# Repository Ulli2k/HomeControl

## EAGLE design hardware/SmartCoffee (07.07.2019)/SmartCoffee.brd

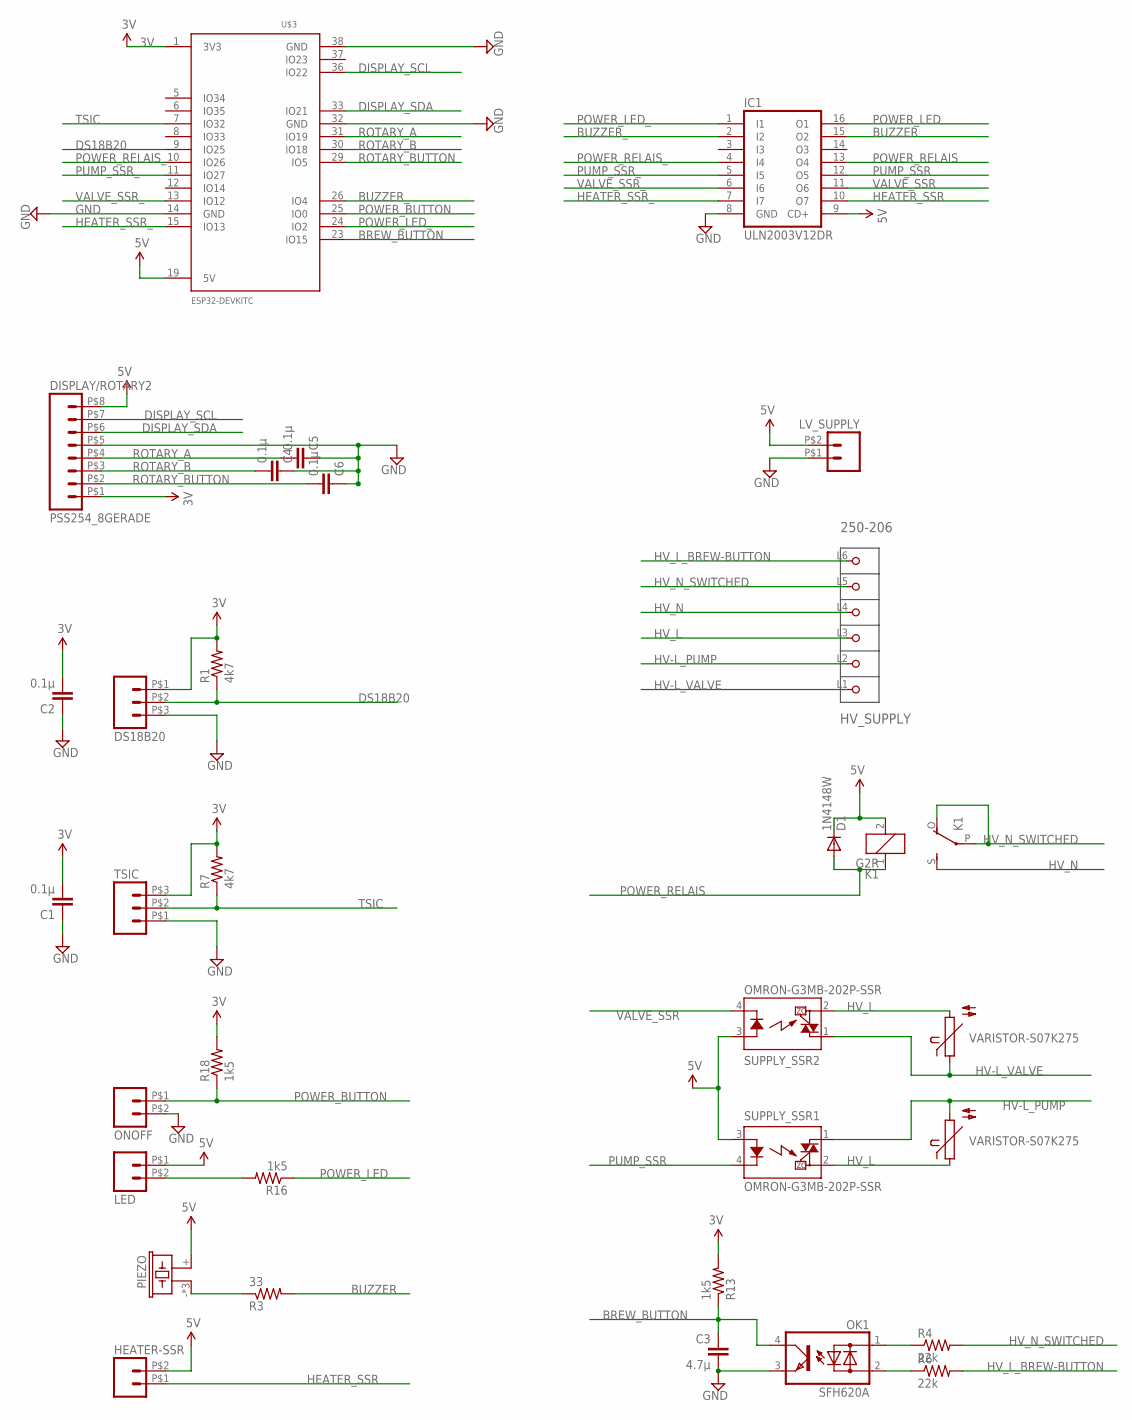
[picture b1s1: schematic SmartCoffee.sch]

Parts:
C1, C2, C4, C5, C6: 0.1µ; 0603-CAP
C3: 4.7µ; 0805-CAP
D1: 1N4148W; SOD123
DISPLAY/ROTARY2: PSS254_8GERADE; 08G
DS18B20: PSS254_3GERADE; 03G
HEATER-SSR: PSS254_2GERADE; 02G
HV_SUPPLY: 250-206; P-250-206
IC1: ULN2003V12DR; SO16
K1: G2R
LED: PSS254_2GERADE; 02G
LV_SUPPLY: PSS254_2GERADE; 02G
OK1: SFH620A; DIL04
ONOFF: PSS254_2GERADE; 02G
PIEZO: BUZZER-PIEZO_SMD
R1, R7: 4k7; 0603-RES
R3: 33; 0603-RES
R4, R6: 22k; RES_UPRIGHT
R5, R8: VARISTOR-S07K275; S07K275
R13, R16, R18: 1k5; 0603-RES
SUPPLY_SSR1, SUPPLY_SSR2: OMRON-G3MB-202P-SSR
TSIC: PSS254_3GERADE; 03G
U$3: ESP32DEVKITC; ESP32-DEVKITC

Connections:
3V: C1.2, C2.2, DISPLAY/ROTARY2.P$1 (1), DS18B20.P$1 (1), R1.2, R7.2, R13.2, R18.2, TSIC.P$3 (3), U$3.1 (3V3)
BREW_BUTTON: C3.1, OK1.4 (C), R13.1, U$3.23 (IO15)
BUZZER: IC1.15 (O2), R3.2
BUZZER_: IC1.2 (I2), U$3.26 (IO4)
DISPLAY_SCL: DISPLAY/ROTARY2.P$7 (7), U$3.36 (IO22)
DISPLAY_SDA: DISPLAY/ROTARY2.P$6 (6), U$3.33 (IO21)
DS18B20: DS18B20.P$2 (2), R1.1, U$3.9 (IO25)
GND: C1.1, C2.1, C3.2, C4.1, C5.1, C6.1, DISPLAY/ROTARY2.P$5 (5), DS18B20.P$3 (3), IC1.8 (GND), LV_SUPPLY.P$1 (1), OK1.3 (E), ONOFF.P$2 (2), TSIC.P$1 (1), U$3.14 (GND), U$3.32 (GND), U$3.38 (GND)
HEATER_SSR: HEATER-SSR.P$1 (1), IC1.10 (O7)
HEATER_SSR_: IC1.7 (I7), U$3.15 (IO13)
HV-L_PUMP: HV_SUPPLY.L2 (P2), R8.2, SUPPLY_SSR1.1 (DS1)
HV-L_VALVE: HV_SUPPLY.L1 (P1), R5.1, SUPPLY_SSR2.1 (DS1)
HV_L: HV_SUPPLY.L3 (P3), R5.2, R8.1, SUPPLY_SSR1.2 (DS2), SUPPLY_SSR2.2 (DS2)
HV_L_BREW-BUTTON: HV_SUPPLY.L6 (P6), R6.2
HV_N: HV_SUPPLY.L4 (P4), K1.S
HV_N_SWITCHED: HV_SUPPLY.L5 (P5), K1.O, K1.P, R4.2
unnamed: LED.P$2 (2), R16.2
unnamed: OK1.1 (AC1), R4.1
unnamed: PIEZO.- (2), PIEZO.DUMMY (2), PIEZO.DUMMY1 (2), R3.1
unnamed: OK1.2 (AC2), R6.1
POWER_BUTTON: ONOFF.P$1 (1), R18.1, U$3.25 (IO0)
POWER_LED: IC1.16 (O1), R16.1
POWER_LED_: IC1.1 (I1), U$3.24 (IO2)
POWER_RELAIS: D1.A, IC1.13 (O4), K1.1
POWER_RELAIS_: IC1.4 (I4), U$3.10 (IO26)
PUMP_SSR: IC1.12 (O5), SUPPLY_SSR1.4 (K)
PUMP_SSR_: IC1.5 (I5), U$3.11 (IO27)
ROTARY_A: C5.2, DISPLAY/ROTARY2.P$4 (4), U$3.31 (IO19)
ROTARY_B: C4.2, DISPLAY/ROTARY2.P$3 (3), U$3.30 (IO18)
ROTARY_BUTTON: C6.2, DISPLAY/ROTARY2.P$2 (2), U$3.29 (IO5)
TSIC: R7.1, TSIC.P$2 (2), U$3.7 (IO32)
VALVE_SSR: IC1.11 (O6), SUPPLY_SSR2.4 (K)
VALVE_SSR_: IC1.6 (I6), U$3.13 (IO12)
VCC: D1.C, DISPLAY/ROTARY2.P$8 (8), HEATER-SSR.P$2 (2), IC1.9 (CD+), K1.2, LED.P$1 (1), LV_SUPPLY.P$2 (2), PIEZO.+ (1), SUPPLY_SSR1.3 (A), SUPPLY_SSR2.3 (A), U$3.19 (5V)

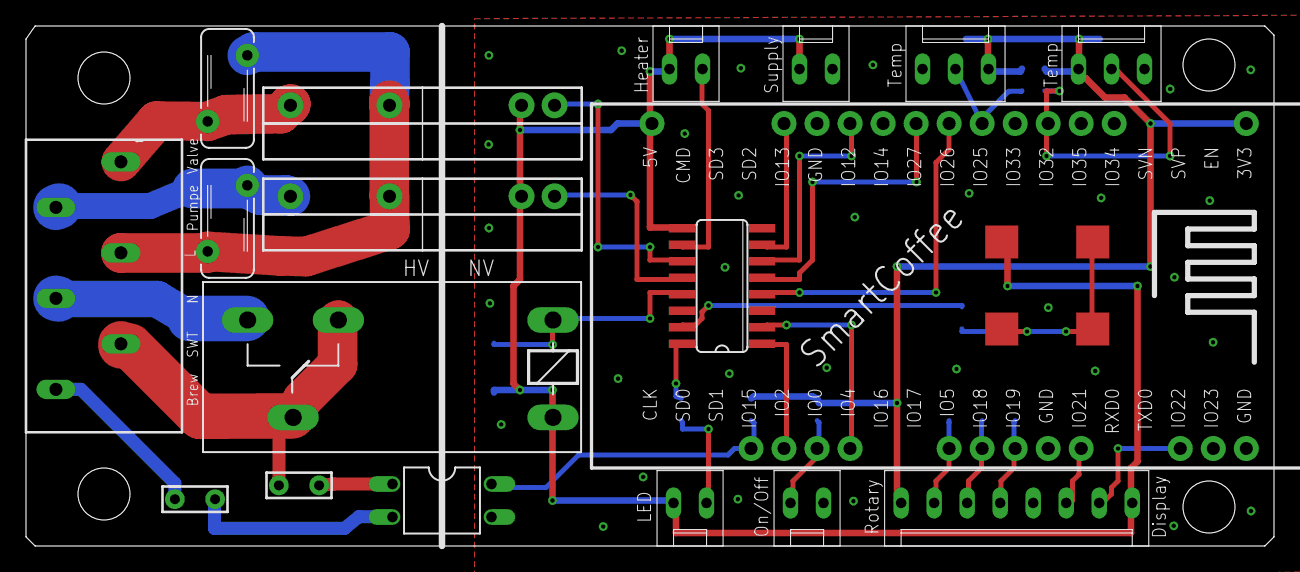
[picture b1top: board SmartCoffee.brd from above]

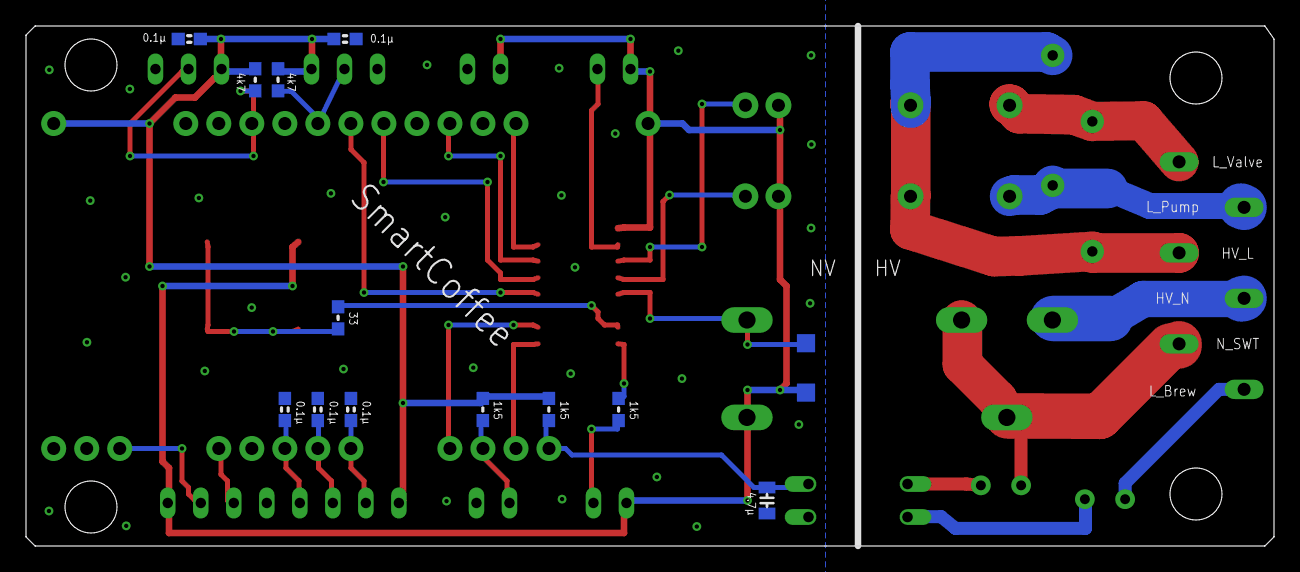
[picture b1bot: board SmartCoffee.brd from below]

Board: 2 copper layers, 96.0 x 40.0 mm, 32 parts (13 on the bottom side), 34 nets.

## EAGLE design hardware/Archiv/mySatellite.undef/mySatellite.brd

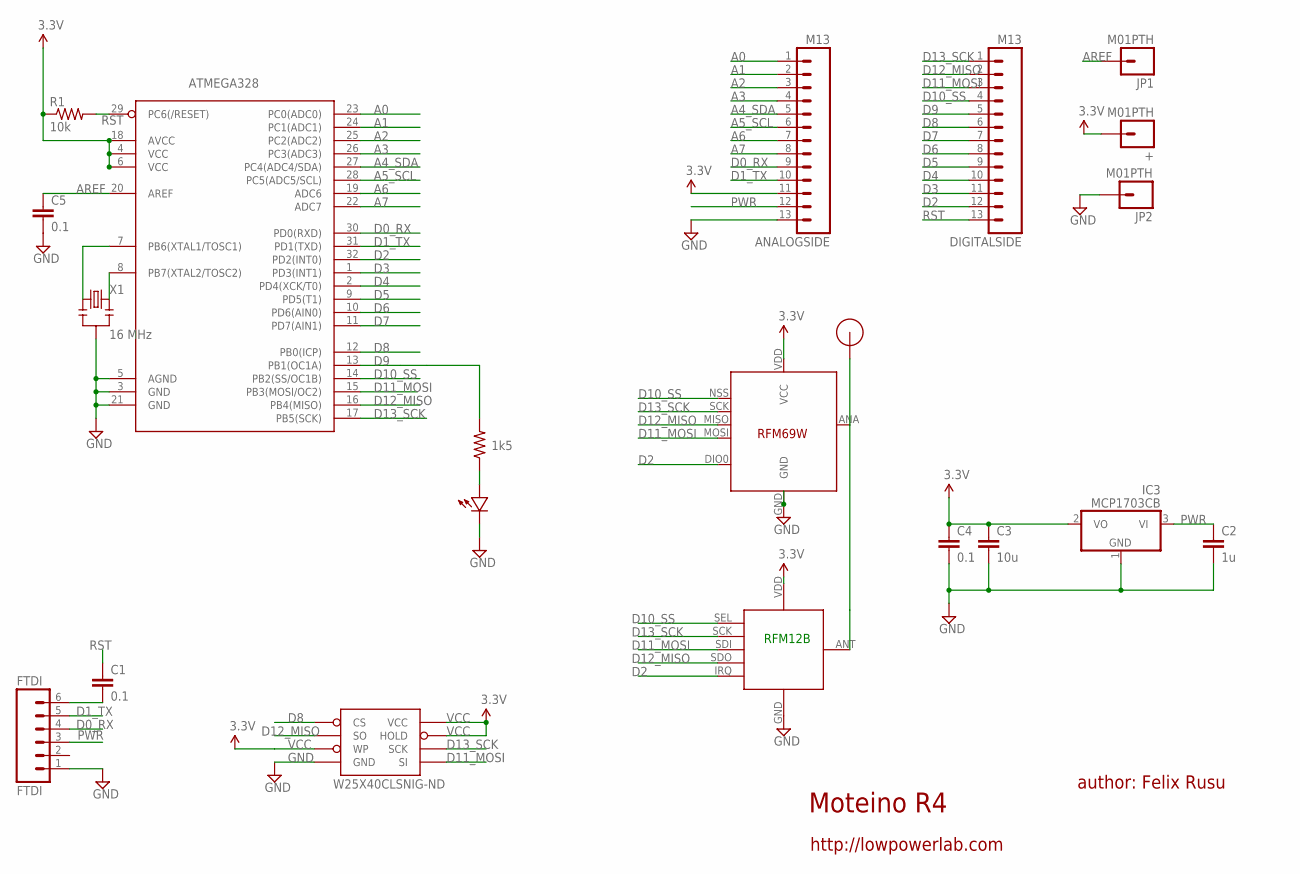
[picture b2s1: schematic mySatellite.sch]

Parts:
+: M01PTH; 1X01
ANALOGSIDE: M13; 1X13
ATMEGA328: ATMega-328; TQFP32-08
C1, C4, C5: 0.1; 0603-CAP
C2: 1u; 0603-CAP
C3: 10u; 0805-CAP
DIGITALSIDE: M13; 1X13
FTDI: FTDI; 1X06
IC3: MCP1703CB; SOT23
JP1, JP2: M01PTH; 1X01
R1: 10k; 0603-RES
R2: 1k5; 0603-RES
RFM12B: RFM12B_MINPADS; RFM12B-MINPADS
U$1: RFM12B_ANTENNA; RFM12B-ANTENNA
U$2: LED0603; 0603-LED
U$5: RFM69; RFM69W-MINPADS
W25X40CLSNIG-ND: AT25F512BWIDE_5.3MM; SO08WIDE
X1: 16 MHz; RESONATOR-SMD

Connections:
A0: ANALOGSIDE.1, ATMEGA328.23 (PC0(ADC0))
A1: ANALOGSIDE.2, ATMEGA328.24 (PC1(ADC1))
A2: ANALOGSIDE.3, ATMEGA328.25 (PC2(ADC2))
A3: ANALOGSIDE.4, ATMEGA328.26 (PC3(ADC3))
A4_SDA: ANALOGSIDE.5, ATMEGA328.27 (PC4(ADC4/SDA))
A5_SCL: ANALOGSIDE.6, ATMEGA328.28 (PC5(ADC5/SCL))
A6: ANALOGSIDE.7, ATMEGA328.19 (ADC6)
A7: ANALOGSIDE.8, ATMEGA328.22 (ADC7)
AREF: ATMEGA328.20 (AREF), C5.1, JP1.1
D0_RX: ANALOGSIDE.9, ATMEGA328.30 (PD0(RXD)), FTDI.4
D1_TX: ANALOGSIDE.10, ATMEGA328.31 (PD1(TXD)), FTDI.5
D2: ATMEGA328.32 (PD2(INT0)), DIGITALSIDE.12, RFM12B.IRQ, U$5.DIO0
D3: ATMEGA328.1 (PD3(INT1)), DIGITALSIDE.11
D4: ATMEGA328.2 (PD4(XCK/T0)), DIGITALSIDE.10
D5: ATMEGA328.9 (PD5(T1)), DIGITALSIDE.9
D6: ATMEGA328.10 (PD6(AIN0)), DIGITALSIDE.8
D7: ATMEGA328.11 (PD7(AIN1)), DIGITALSIDE.7
D8: ATMEGA328.12 (PB0(ICP)), DIGITALSIDE.6, W25X40CLSNIG-ND.1 (CS)
D9: ATMEGA328.13 (PB1(OC1A)), DIGITALSIDE.5, R2.2
D10_SS: ATMEGA328.14 (PB2(SS/OC1B)), DIGITALSIDE.4, RFM12B.SEL, U$5.NSS (SEL)
D11_MOSI: ATMEGA328.15 (PB3(MOSI/OC2)), DIGITALSIDE.3, RFM12B.SDI (SDI/MOSI), U$5.MOSI, W25X40CLSNIG-ND.5 (SI)
D12_MISO: ATMEGA328.16 (PB4(MISO)), DIGITALSIDE.2, RFM12B.SDO (SDO/MISO), U$5.MISO, W25X40CLSNIG-ND.2 (SO)
D13_SCK: ATMEGA328.17 (PB5(SCK)), DIGITALSIDE.1, RFM12B.SCK, U$5.SCK, W25X40CLSNIG-ND.6 (SCK)
GND: ANALOGSIDE.13, ATMEGA328.3 (GND), ATMEGA328.5 (AGND), ATMEGA328.21 (GND), C2.2, C3.2, C4.2, C5.2, FTDI.1, IC3.1 (GND), JP2.1, RFM12B.GND, U$2.MINUS, U$5.GND, W25X40CLSNIG-ND.4 (GND), X1.2
unnamed: ATMEGA328.7 (PB6(XTAL1/TOSC1)), X1.1
unnamed: R2.1, U$2.PLUS
unnamed: RFM12B.ANT, U$1.P$1, U$5.ANA (ANT)
unnamed: C1.2, FTDI.6
unnamed: ATMEGA328.8 (PB7(XTAL2/TOSC2)), X1.3
PWR: ANALOGSIDE.12, C2.1, FTDI.3, IC3.3 (VI)
RST: ATMEGA328.29 (PC6(/RESET)), C1.1, DIGITALSIDE.13, R1.2
VCC: +.1, ANALOGSIDE.11, ATMEGA328.4 (VCC), ATMEGA328.6 (VCC), ATMEGA328.18 (AVCC), C3.1, C4.1, IC3.2 (VO), R1.1, RFM12B.VDD, U$5.VDD (VCC), W25X40CLSNIG-ND.3 (WP), W25X40CLSNIG-ND.7 (HOLD), W25X40CLSNIG-ND.8 (VCC)

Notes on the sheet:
Moteino R4
author: Felix Rusu
http://lowpowerlab.com
RFM12B

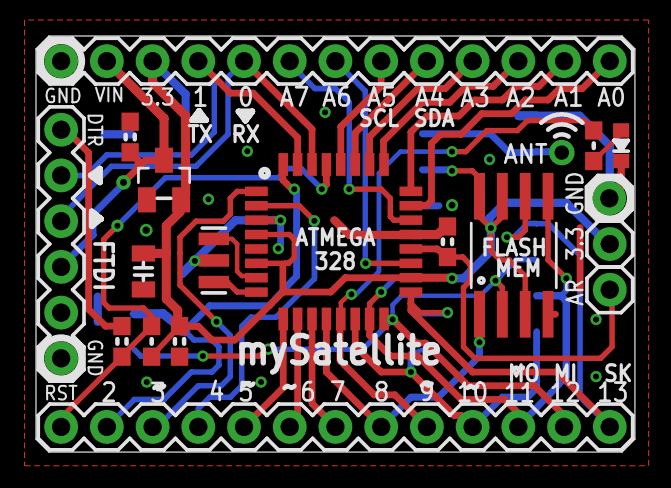
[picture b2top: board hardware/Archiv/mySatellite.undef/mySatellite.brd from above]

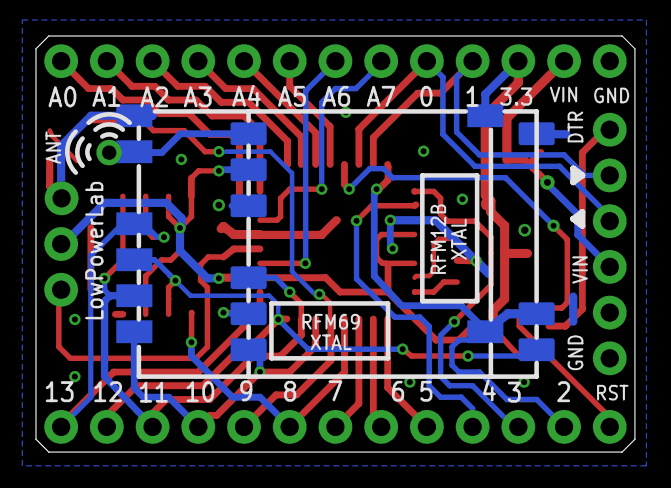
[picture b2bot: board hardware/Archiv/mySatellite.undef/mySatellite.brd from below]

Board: 2 copper layers, 33.3 x 23.1 mm, 21 parts (2 on the bottom side), 32 nets.

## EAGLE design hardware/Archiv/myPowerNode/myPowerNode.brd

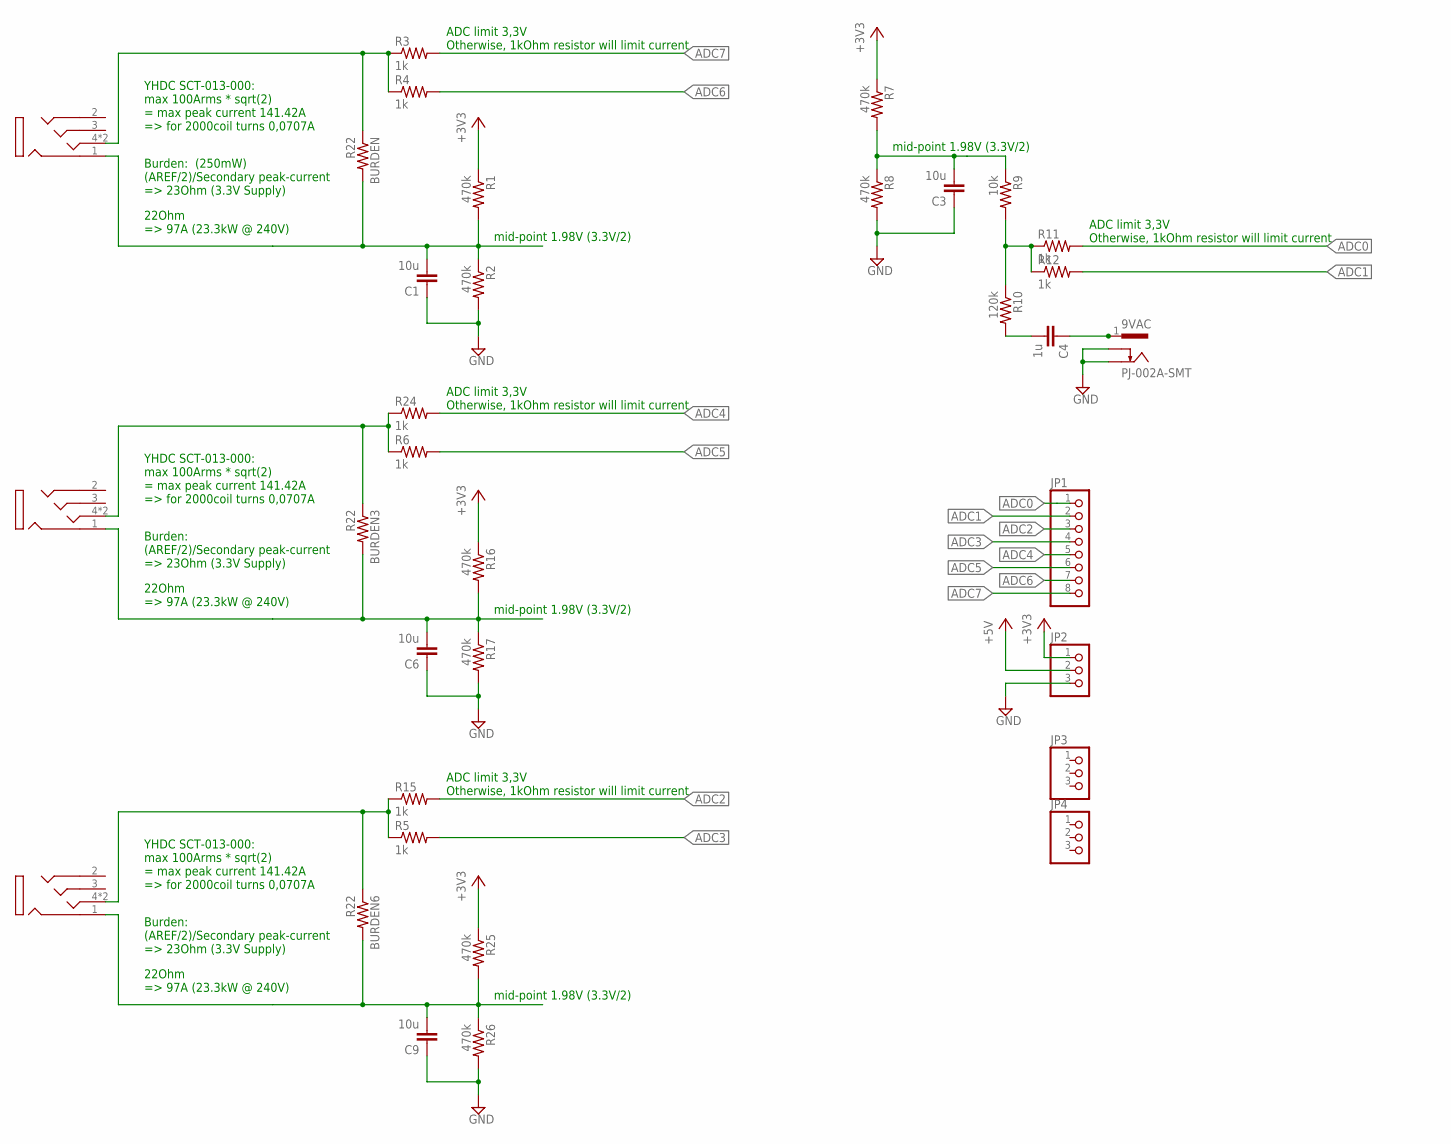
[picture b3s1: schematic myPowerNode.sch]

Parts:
9VAC: PJ-002A-SMT; CUI_PJ-002B-SMT
BURDEN, BURDEN3, BURDEN6: R22; R0805
C1, C3, C6, C9: 10u; 0603-CAP
C4: 1u; 0603-CAP
CT1, CT4, CT7: 1503_13; 1503-03
JP1: PINHD-1X8CLEANBIG; 1X08-CLEANBIG
JP2, JP3, JP4: PINHD-1X3CB; 1X03-CLEANBIG
R1, R2, R7, R8, R16, R17, R25, R26: 470k; 0603-RES
R3, R4, R5, R6, R11, R12, R15, R24: 1k; 0603-RES
R9: 10k; 0603-RES
R10: 120k; 0603-RES

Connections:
+3V3: JP2.1, R1.1, R7.1, R16.1, R25.1
+5V: JP2.2
ADC0: JP1.1, R11.2
ADC1: JP1.2, R12.2
ADC2: JP1.3, R15.2
ADC3: JP1.4, R5.2
ADC4: JP1.5, R24.2
ADC5: JP1.6, R6.2
ADC6: JP1.7, R4.2
ADC7: JP1.8, R3.2
GND: 9VAC.3, 9VAC.4, C1.1, C3.1, C6.1, C9.1, JP2.3, R2.2, R8.2, R17.2, R26.2
unnamed: BURDEN.2, C1.2, CT1.1, R1.2, R2.1
unnamed: BURDEN.1, CT1.4, CT1.4-2 (4), R3.1, R4.1
unnamed: C3.2, R7.2, R8.1, R9.1
unnamed: R9.2, R10.1, R11.1, R12.1
unnamed: C4.2, R10.2
unnamed: 9VAC.1, 9VAC.2, C4.1
unnamed: BURDEN3.2, C6.2, CT4.1, R16.2, R17.1
unnamed: BURDEN3.1, CT4.4, CT4.4-2 (4), R6.1, R24.1
unnamed: BURDEN6.2, C9.2, CT7.1, R25.2, R26.1
unnamed: BURDEN6.1, CT7.4, CT7.4-2 (4), R5.1, R15.1

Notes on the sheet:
mid-point 1.98V (3.3V/2)
ADC limit 3,3V Otherwise, 1kOhm resistor will limit current
YHDC SCT-013-000: max 100Arms * sqrt(2) = max peak current 141.42A => for 2000coil turns 0,0707A
Burden: (250mW) (AREF/2)/Secondary peak-current => 23Ohm (3.3V Supply)
22Ohm => 97A (23.3kW @ 240V)
Burden: (AREF/2)/Secondary peak-current => 23Ohm (3.3V Supply)

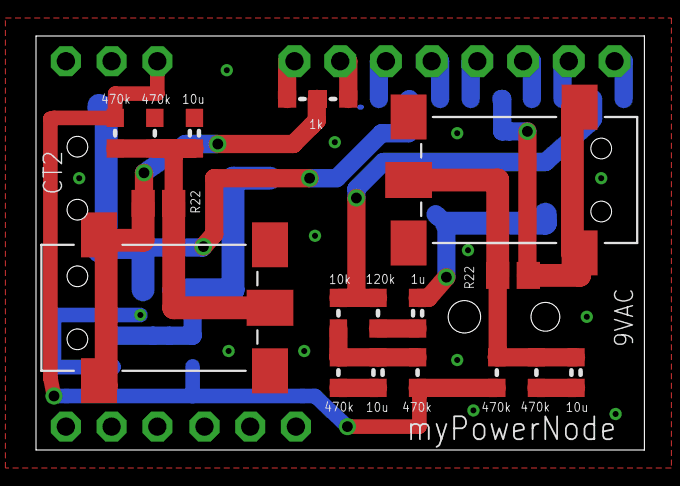
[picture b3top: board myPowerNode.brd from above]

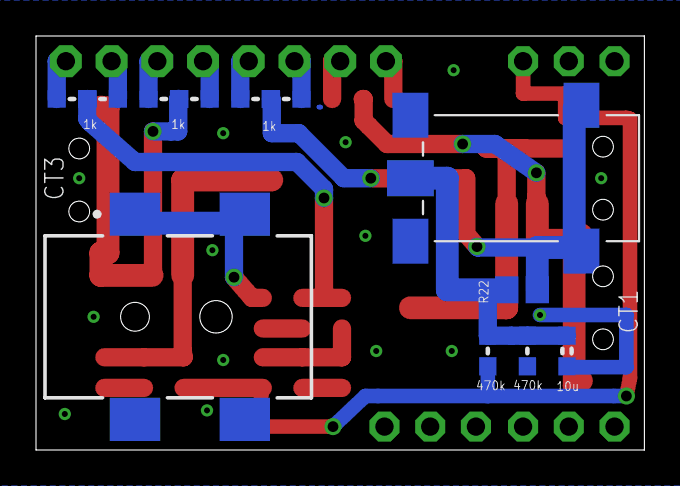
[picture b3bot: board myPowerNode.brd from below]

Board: 2 copper layers, 33.8 x 23.0 mm, 34 parts (12 on the bottom side), 20 nets.

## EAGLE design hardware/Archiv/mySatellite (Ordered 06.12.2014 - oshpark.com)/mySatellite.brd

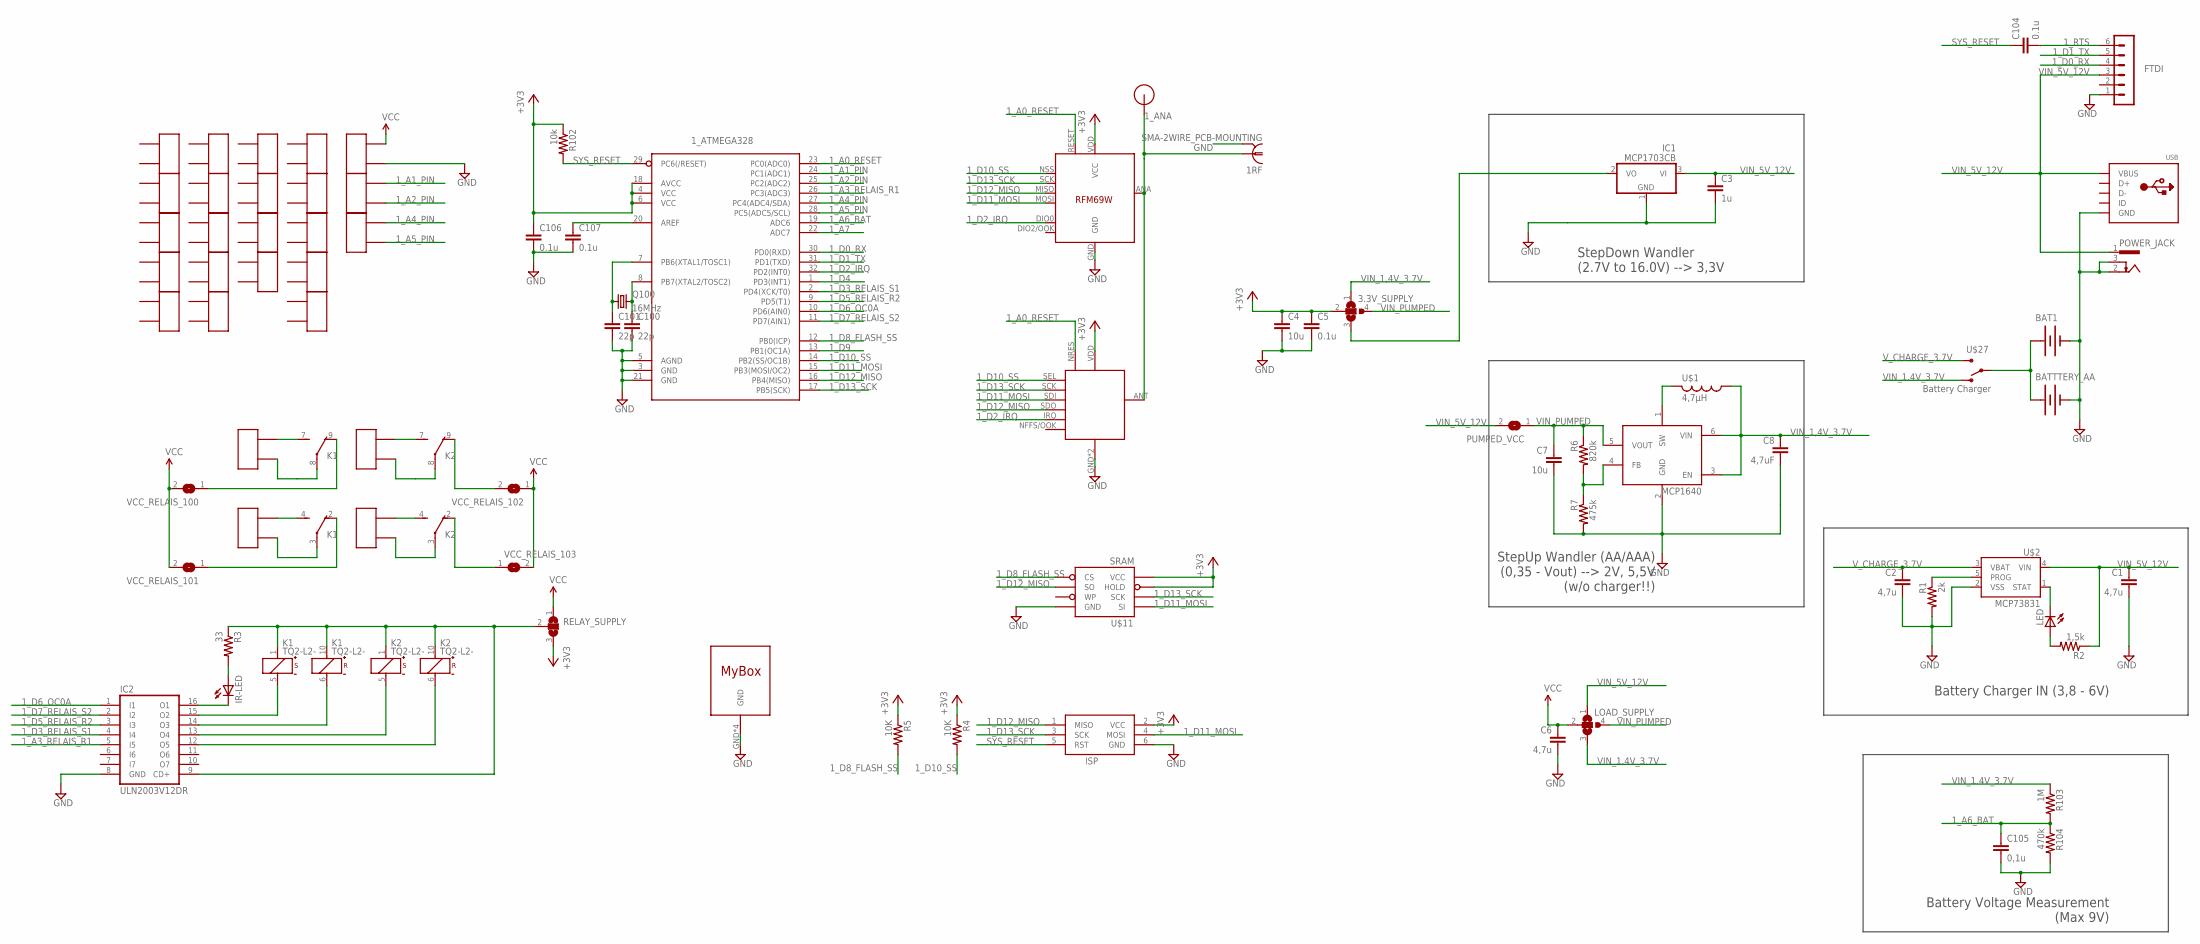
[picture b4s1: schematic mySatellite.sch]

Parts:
1RF: SMA-2WIRE_PCB-MOUNTING; J01151A0931
1_ATMEGA328: ATMega-328; TQFP32-08
1_RFM12: RFM12B_MINPADS; RFM12B-MINPADS
1_RFM69: RFM69_MINIPADS; RFM69W-MINPADS
3.3V_SUPPLY: SJ3W; SJ_3
ADC1, ADC2: HDR_2PIN; 1X02_NS
BAT1: BATTERY; BATTERY-CR2
BATTTERY_AA: BATTERYAA; BATTERY-AA
C1, C2, C6: 4,7u; 0603-CAP
C3: 1u; 0603-CAP
C4, C7: 10u; 0603-CAP
C5, C104, C106, C107: 0.1u; 0603-CAP
C8: 4,7uF; 0603-CAP
C100, C101: 22p; 0603-CAP
C105: 0,1u; 0603-CAP
FTDI: FTDI; MA06-1
IC1: MCP1703CB; SOT23
IC2: ULN2003V12DR; SO16
IR-LED: LED5MM
IR/RELAY_SATELLITE: MY-BOX
ISP: AVRISP; AVRISP-EDGE
K1, K2: TQ2-L2-; TQ2; MPN TQ2-L2-3V
LED: LED3MM
LOAD_SUPPLY: SJ3W; SJ_3
POWER_JACK: LUMBERG_1613-200-62; 733980-62
PUMPED_VCC: SJ
Q100: 16MHz; HC49/S
R1: 2k; 0603-RES
R2: 1,5k; 0603-RES
R3: 33; 0603-RES
R4, R5: 10K; 0603-RES
R6: 820k; 0603-RES
R7: 475k; 0603-RES
R102: 10k; 0603-RES
R103: 1M; 0603-RES
R104: 470k; 0603-RES
RELAY_SUPPLY: SJ2W; SJ_2
U1: MCP1640; SOT23-6
U$1: 4,7µH; INDUCTOR_EPCOS
U$2: MCP73831; SOT23-5
U$3, U$5, U$6, U$7, U$8, U$9, U$10, U$12, U$13, U$14, U$15, U$16, U$17, U$19, U$20, U$21, U$22, U$23, U$24, U$25, U$26, U$29, U$30: HDR_2PIN; 1X02_NS
U$11: SRAM; LOWPOWERLAB_SO08
U$18: RFM12B_ANTENNA; RFM12B-ANTENNA
U$27: Battery Charger; SSK-1202
USB: USBMINIB; USB-MINIB
VCC: HDR_2PIN; 1X02_NS
VCC_RELAIS_100, VCC_RELAIS_101, VCC_RELAIS_102, VCC_RELAIS_103: SJ

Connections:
1_A0_RESET: 1_ATMEGA328.23 (PC0(ADC0)), 1_RFM12.NRES, 1_RFM69.RESET
1_A1_PIN: 1_ATMEGA328.24 (PC1(ADC1)), ADC1.1
1_A2_PIN: 1_ATMEGA328.25 (PC2(ADC2)), ADC1.2
1_A3_RELAIS_R1: 1_ATMEGA328.26 (PC3(ADC3)), IC2.5 (I5)
1_A4_PIN: 1_ATMEGA328.27 (PC4(ADC4/SDA)), ADC2.1
1_A5_PIN: 1_ATMEGA328.28 (PC5(ADC5/SCL)), ADC2.2
1_A6_BAT: 1_ATMEGA328.19 (ADC6), C105.1, R103.2, R104.1
1_A7: 1_ATMEGA328.22 (ADC7)
1_ANA: 1RF.1, 1_RFM12.ANT, 1_RFM69.ANA (ANT), U$18.P$1
1_AREF: 1_ATMEGA328.20 (AREF), C107.1
1_D0_RX: 1_ATMEGA328.30 (PD0(RXD)), FTDI.4
1_D1_TX: 1_ATMEGA328.31 (PD1(TXD)), FTDI.5
1_D2_IRQ: 1_ATMEGA328.32 (PD2(INT0)), 1_RFM12.IRQ, 1_RFM69.DIO0 (DIO0/IRQ)
1_D3_RELAIS_S1: 1_ATMEGA328.2 (PD4(XCK/T0)), IC2.4 (I4)
1_D4: 1_ATMEGA328.1 (PD3(INT1))
1_D5_RELAIS_R2: 1_ATMEGA328.9 (PD5(T1)), IC2.3 (I3)
1_D6_OC0A: 1_ATMEGA328.10 (PD6(AIN0)), IC2.1 (I1)
1_D7_RELAIS_S2: 1_ATMEGA328.11 (PD7(AIN1)), IC2.2 (I2)
1_D8_FLASH_SS: 1_ATMEGA328.12 (PB0(ICP)), R5.2, U$11.1_CS (CS)
1_D9: 1_ATMEGA328.13 (PB1(OC1A))
1_D10_SS: 1_ATMEGA328.14 (PB2(SS/OC1B)), 1_RFM12.SEL, 1_RFM69.NSS (SEL), R4.2
1_D11_MOSI: 1_ATMEGA328.15 (PB3(MOSI/OC2)), 1_RFM12.SDI (SDI/MOSI), 1_RFM69.MOSI, ISP.4 (MOSI), U$11.5_SI (SI)
1_D12_MISO: 1_ATMEGA328.16 (PB4(MISO)), 1_RFM12.SDO (SDO/MISO), 1_RFM69.MISO, ISP.1 (MISO), U$11.2_SO (SO)
1_D13_SCK: 1_ATMEGA328.17 (PB5(SCK)), 1_RFM12.SCK, 1_RFM69.SCK, ISP.3 (SCK), U$11.6_SCK (SCK)
1_RTS: C104.2, FTDI.6
+3V3: 1_ATMEGA328.4 (VCC), 1_ATMEGA328.6 (VCC), 1_ATMEGA328.18 (AVCC), 1_RFM12.VDD, 1_RFM69.VDD (VCC), 3.3V_SUPPLY.2, C4.1, C5.1, C106.1, ISP.2 (VCC), R4.1, R5.1, R102.1, RELAY_SUPPLY.3, U$11.7_HOLD (HOLD), U$11.8_VCC (VCC)
BAT+: BAT1.PWR@1 (+), BATTTERY_AA.PWR@1 (+), U$27.P
GND: 1RF.G@1 (2), 1RF.G@2 (2), 1RF.G@3 (2), 1RF.G@4 (2), 1_ATMEGA328.3 (GND), 1_ATMEGA328.5 (AGND), 1_ATMEGA328.21 (GND), 1_RFM12.GND, 1_RFM12.GND1 (GND), 1_RFM69.GND, BAT1.GND@1 (-), BATTTERY_AA.GND@1 (-), C1.2, C2.2, C3.2, C4.2, C5.2, C6.2, C7.2, C8.2, C100.2, C101.2, C105.2, C106.2, C107.2, FTDI.1, IC1.1 (GND), IC2.8 (GND), IR/RELAY_SATELLITE.GND, IR/RELAY_SATELLITE.GND1, IR/RELAY_SATELLITE.GND2, IR/RELAY_SATELLITE.GND3, ISP.6 (GND), POWER_JACK.2, POWER_JACK.3, R1.2, R7.2, R104.2, U1.2 (GND), U$2.2 (VSS), U$11.4_GND (GND), USB.GND, VCC.2
unnamed: 1_ATMEGA328.7 (PB6(XTAL1/TOSC1)), C101.1, Q100.1
unnamed: R1.1, U$2.5 (PROG)
unnamed: IR-LED.A, R3.2
unnamed: IC2.16 (O1), IR-LED.K (C)
unnamed: IC2.15 (O2), K1.5 (-)
unnamed: IC2.14 (O3), K1.6 (-)
unnamed: 1_ATMEGA328.8 (PB7(XTAL2/TOSC2)), C100.1, Q100.2
unnamed: LED.K (C), U$2.1 (STAT)
unnamed: 3.3V_SUPPLY.3, IC1.2 (VO)
unnamed: K2.3, U$24.1
unnamed: LED.A, R2.2
unnamed: K1.4 (S), U$22.2
unnamed: K1.8, U$21.1
unnamed: K1.7 (S), U$21.2
unnamed: IC2.13 (O4), K2.5 (-)
unnamed: IC2.12 (O5), K2.6 (-)
unnamed: K2.8, U$23.1
unnamed: K2.4 (S), U$24.2
unnamed: K2.7 (S), U$23.2
unnamed: K1.3, U$22.1
unnamed: K1.2 (O), VCC_RELAIS_101.1
unnamed: IC2.9 (CD+), K1.1 (+), K1.10 (+), K2.1 (+), K2.10 (+), R3.1, RELAY_SUPPLY.2
unnamed: K2.2 (O), VCC_RELAIS_103.1
unnamed: K1.9 (O), VCC_RELAIS_100.1
unnamed: K2.9 (O), VCC_RELAIS_102.2
unnamed: U1.1 (SW), U$1.P$2 (2)
unnamed: R6.2, R7.1, U1.4 (FB)
SYS_RESET: 1_ATMEGA328.29 (PC6(/RESET)), C104.1, ISP.5 (RST), R102.2
VCC: C6.1, LOAD_SUPPLY.2, RELAY_SUPPLY.1, VCC.1, VCC_RELAIS_100.2, VCC_RELAIS_101.2, VCC_RELAIS_102.1, VCC_RELAIS_103.2
VIN_1,4V_3.7V: 3.3V_SUPPLY.1, C8.1, LOAD_SUPPLY.3, R103.1, U1.3 (EN), U1.6 (VIN), U$1.P$1 (1), U$27.O
VIN_5V_12V: C1.1, C3.1, FTDI.3, IC1.3 (VI), LOAD_SUPPLY.1, POWER_JACK.1, PUMPED_VCC.2, R2.1, U$2.4 (VIN), USB.VBUS
VIN_PUMPED: 3.3V_SUPPLY.4, C7.1, LOAD_SUPPLY.4, PUMPED_VCC.1, R6.1, U1.5 (VOUT)
V_CHARGE_3.7V: C2.1, U$2.3 (VBAT), U$27.S

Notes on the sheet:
StepUp Wandler (AA/AAA) (0,35 - Vout) --> 2V, 5,5V (w/o charger!!)
StepDown Wandler (2.7V to 16.0V) --> 3,3V
Battery Charger IN (3,8 - 6V)
Battery Voltage Measurement (Max 9V)

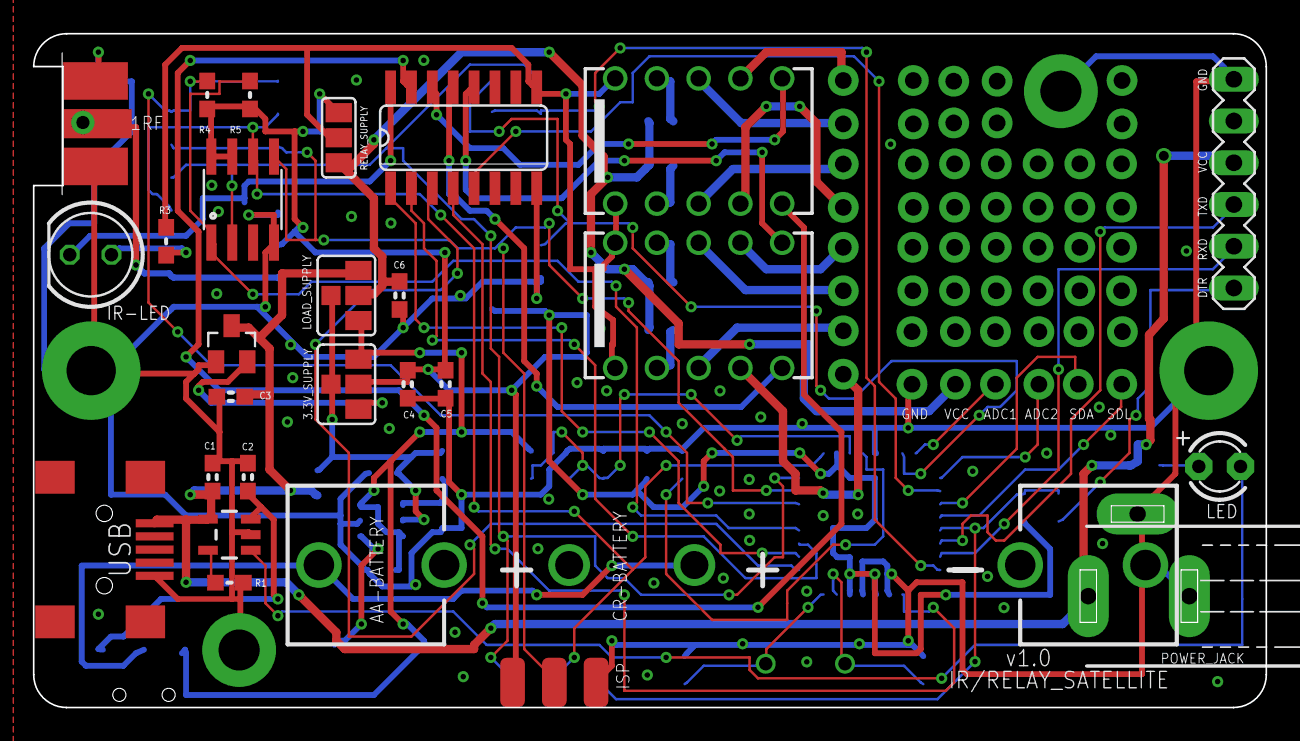
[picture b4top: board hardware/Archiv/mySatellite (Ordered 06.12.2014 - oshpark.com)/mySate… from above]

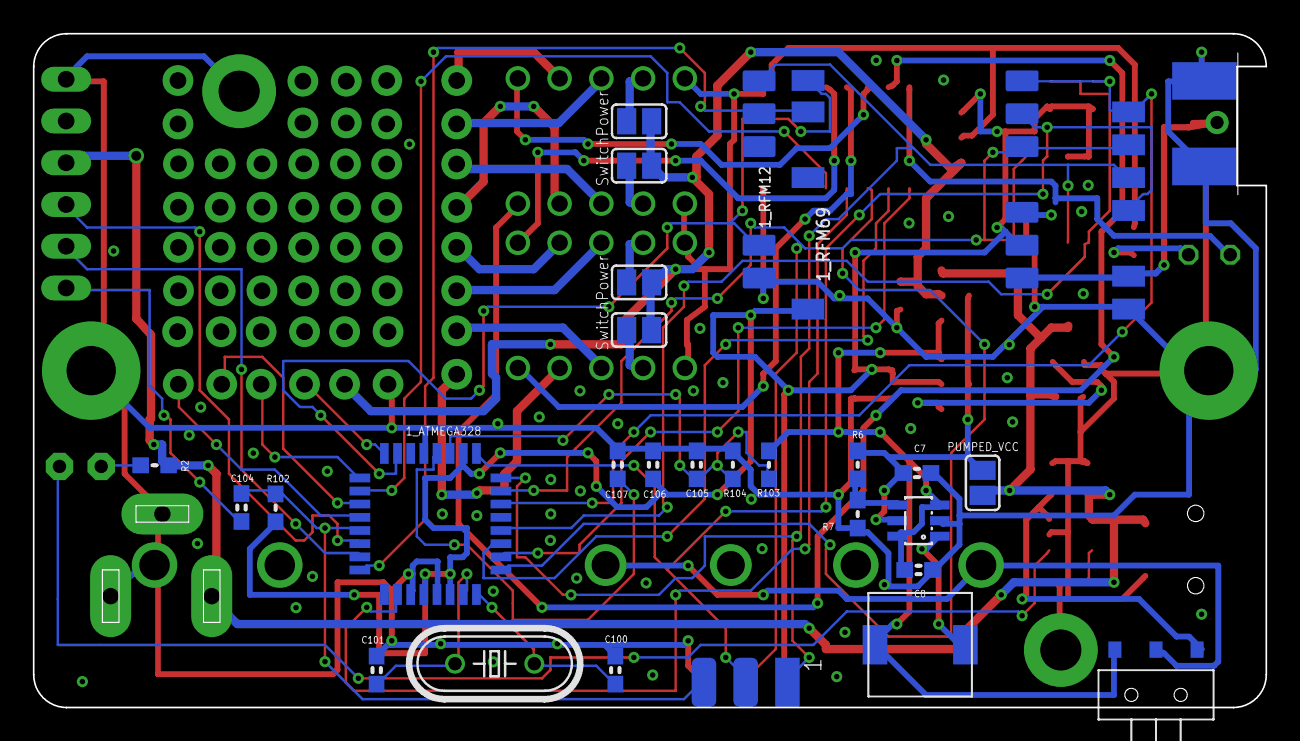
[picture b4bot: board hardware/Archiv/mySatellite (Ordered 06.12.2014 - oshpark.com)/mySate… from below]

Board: 2 copper layers, 75.0 x 41.0 mm, 82 parts (27 on the bottom side), 58 nets.

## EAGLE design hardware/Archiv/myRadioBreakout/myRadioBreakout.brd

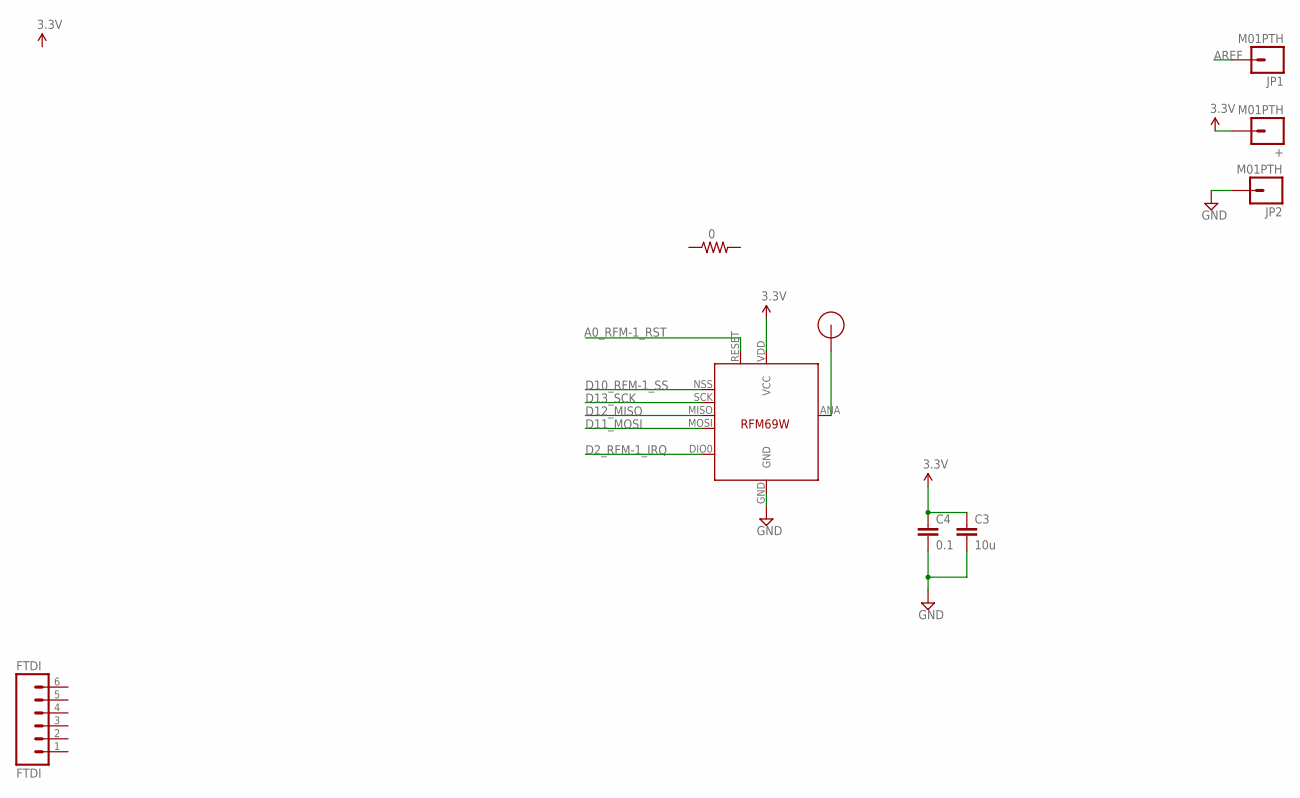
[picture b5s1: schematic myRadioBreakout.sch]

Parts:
+: M01PTH; 1X01
C3: 10u; 0805-CAP
C4: 0.1; 0603-CAP
FTDI: FTDI; 1X06
JP1, JP2: M01PTH; 1X01
R1: 0; 0603-RES
U$1: RFM12B_ANTENNA; RFM12B-ANTENNA
U$5: RFM69_MINIPADS; RFM69W-MINPADS

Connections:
A0_RFM-1_RST: U$5.RESET
AREF: JP1.1
D2_RFM-1_IRQ: U$5.DIO0 (DIO0/IRQ)
D10_RFM-1_SS: U$5.NSS (SEL)
D11_MOSI: U$5.MOSI
D12_MISO: U$5.MISO
D13_SCK: U$5.SCK
GND: C3.2, C4.2, JP2.1, U$5.GND
unnamed: U$1.P$1, U$5.ANA (ANT)
VCC: +.1, C3.1, C4.1, U$5.VDD (VCC)

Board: 2 copper layers, 9 parts (1 on the bottom side), 3 nets, no tracks yet.

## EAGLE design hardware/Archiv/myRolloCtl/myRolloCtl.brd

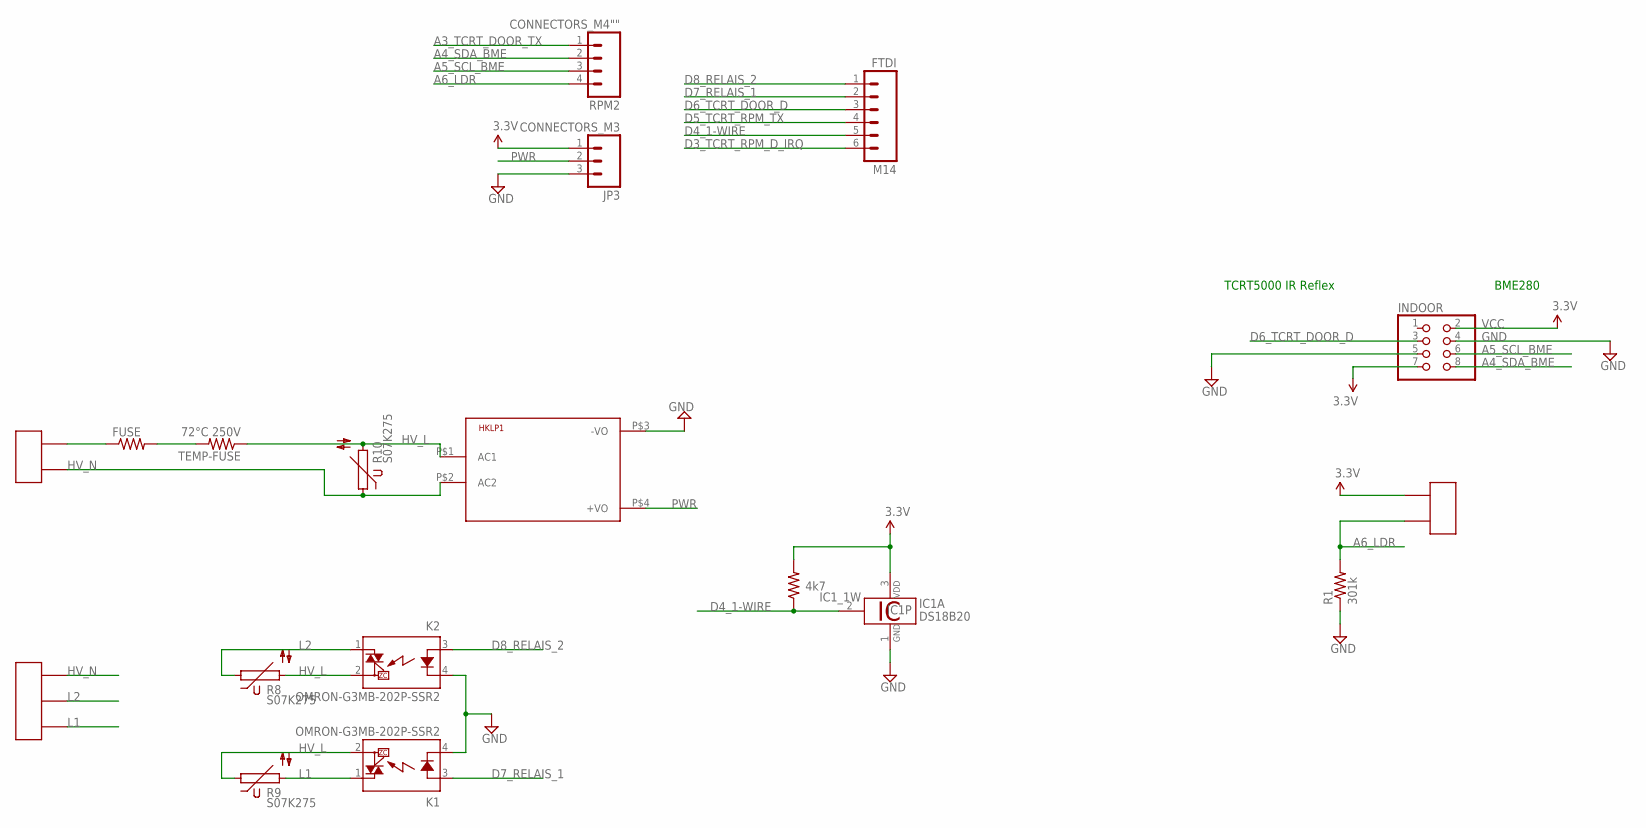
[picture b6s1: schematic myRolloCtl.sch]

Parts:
FUSE: R-US_0613/5V; P0613V
HKLP1: HKLPM01
IC1: DS18B20; TO92-
INDOOR: PINHD-2X4; 2X04
JP3: CONNECTORS_M3; CONNECTORS_1X3
K1, K2: OMRON-G3MB-202P-SSR2; OMRON-G3MB-202P-SSR
M14: FTDI; 1X06
R1: 301k; 0603-RES
R4: 4k7; 0603-RES
R8, R9, R10: S07K275
RPM2: CONNECTORS_M4""; CONNECTORS_1X4
TEMP-FUSE: 72°C 250V; 0207/2V
U$2: HDR_2PIN; 1X02_NS
U$3: HDR_3PIN; 1X03_LUMBERG-KRMC_3,5MM
U$6: HDR_2PIN1X02_3.5MM; 1X02_LUMBERG-KRMC_3,5MM

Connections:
A3_TCRT_DOOR_TX: RPM2.1
A4_SDA_BME: INDOOR.8, RPM2.2
A5_SCL_BME: INDOOR.6, RPM2.3
A6_LDR: R1.2, RPM2.4, U$2.2
D3_TCRT_RPM_D_IRQ: M14.6
D4_1-WIRE: IC1.2 (1W), M14.5, R4.1
D5_TCRT_RPM_TX: M14.4
D6_TCRT_DOOR_D: INDOOR.3, M14.3
D7_RELAIS_1: K1.3 (A), M14.2
D8_RELAIS_2: K2.3 (A), M14.1
GND: HKLP1.P$3 (-VO), IC1.1 (GND), INDOOR.4, INDOOR.5, JP3.3, K1.4 (K), K2.4 (K), R1.1
HV_L: HKLP1.P$1 (AC1), K1.2 (DS2), K2.2 (DS2), R8.2, R9.1, R10.2, TEMP-FUSE.1
HV_N: HKLP1.P$2 (AC2), R10.1, U$3.3, U$6.1
L1: K1.1 (DS1), R9.2, U$3.1
L2: K2.1 (DS1), R8.1, U$3.2
unnamed: FUSE.2, TEMP-FUSE.2
unnamed: FUSE.1, U$6.2
PWR: HKLP1.P$4 (+VO), JP3.2
VCC: IC1.3 (VDD), INDOOR.2, INDOOR.7, JP3.1, R4.2, U$2.1

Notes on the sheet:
TCRT5000 IR Reflex
BME280

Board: 2 copper layers, 18 parts (6 on the bottom side), 16 nets, no tracks yet.

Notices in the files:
parts and their libraries:
SparkFun-Connectors: Licensing: CC v3.0 Share-Alike You are welcome to use this library for commercial purposes.
